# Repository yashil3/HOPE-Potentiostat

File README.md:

# Pocket Potentiostat
IEEE DeCal HOPE Final Project -- Potentiostat for applying cyclic voltammetry to electrolyte

- Blocks A, B, D, and E: uses OPA2277 high-precision operational amplifiers
- Block C: uses TL074 transimpedance amplifier
- Blocks F, G, and H: uses INA128 instrumentational amplifiers
- Block C uses a TL074 Transimpedance Amplifier (TIA). It is cost-effective, but it is not the best option (a really good one would be ~$40)
- May need to fix Rg resistor values based on how much the voltage in the electrodes varies

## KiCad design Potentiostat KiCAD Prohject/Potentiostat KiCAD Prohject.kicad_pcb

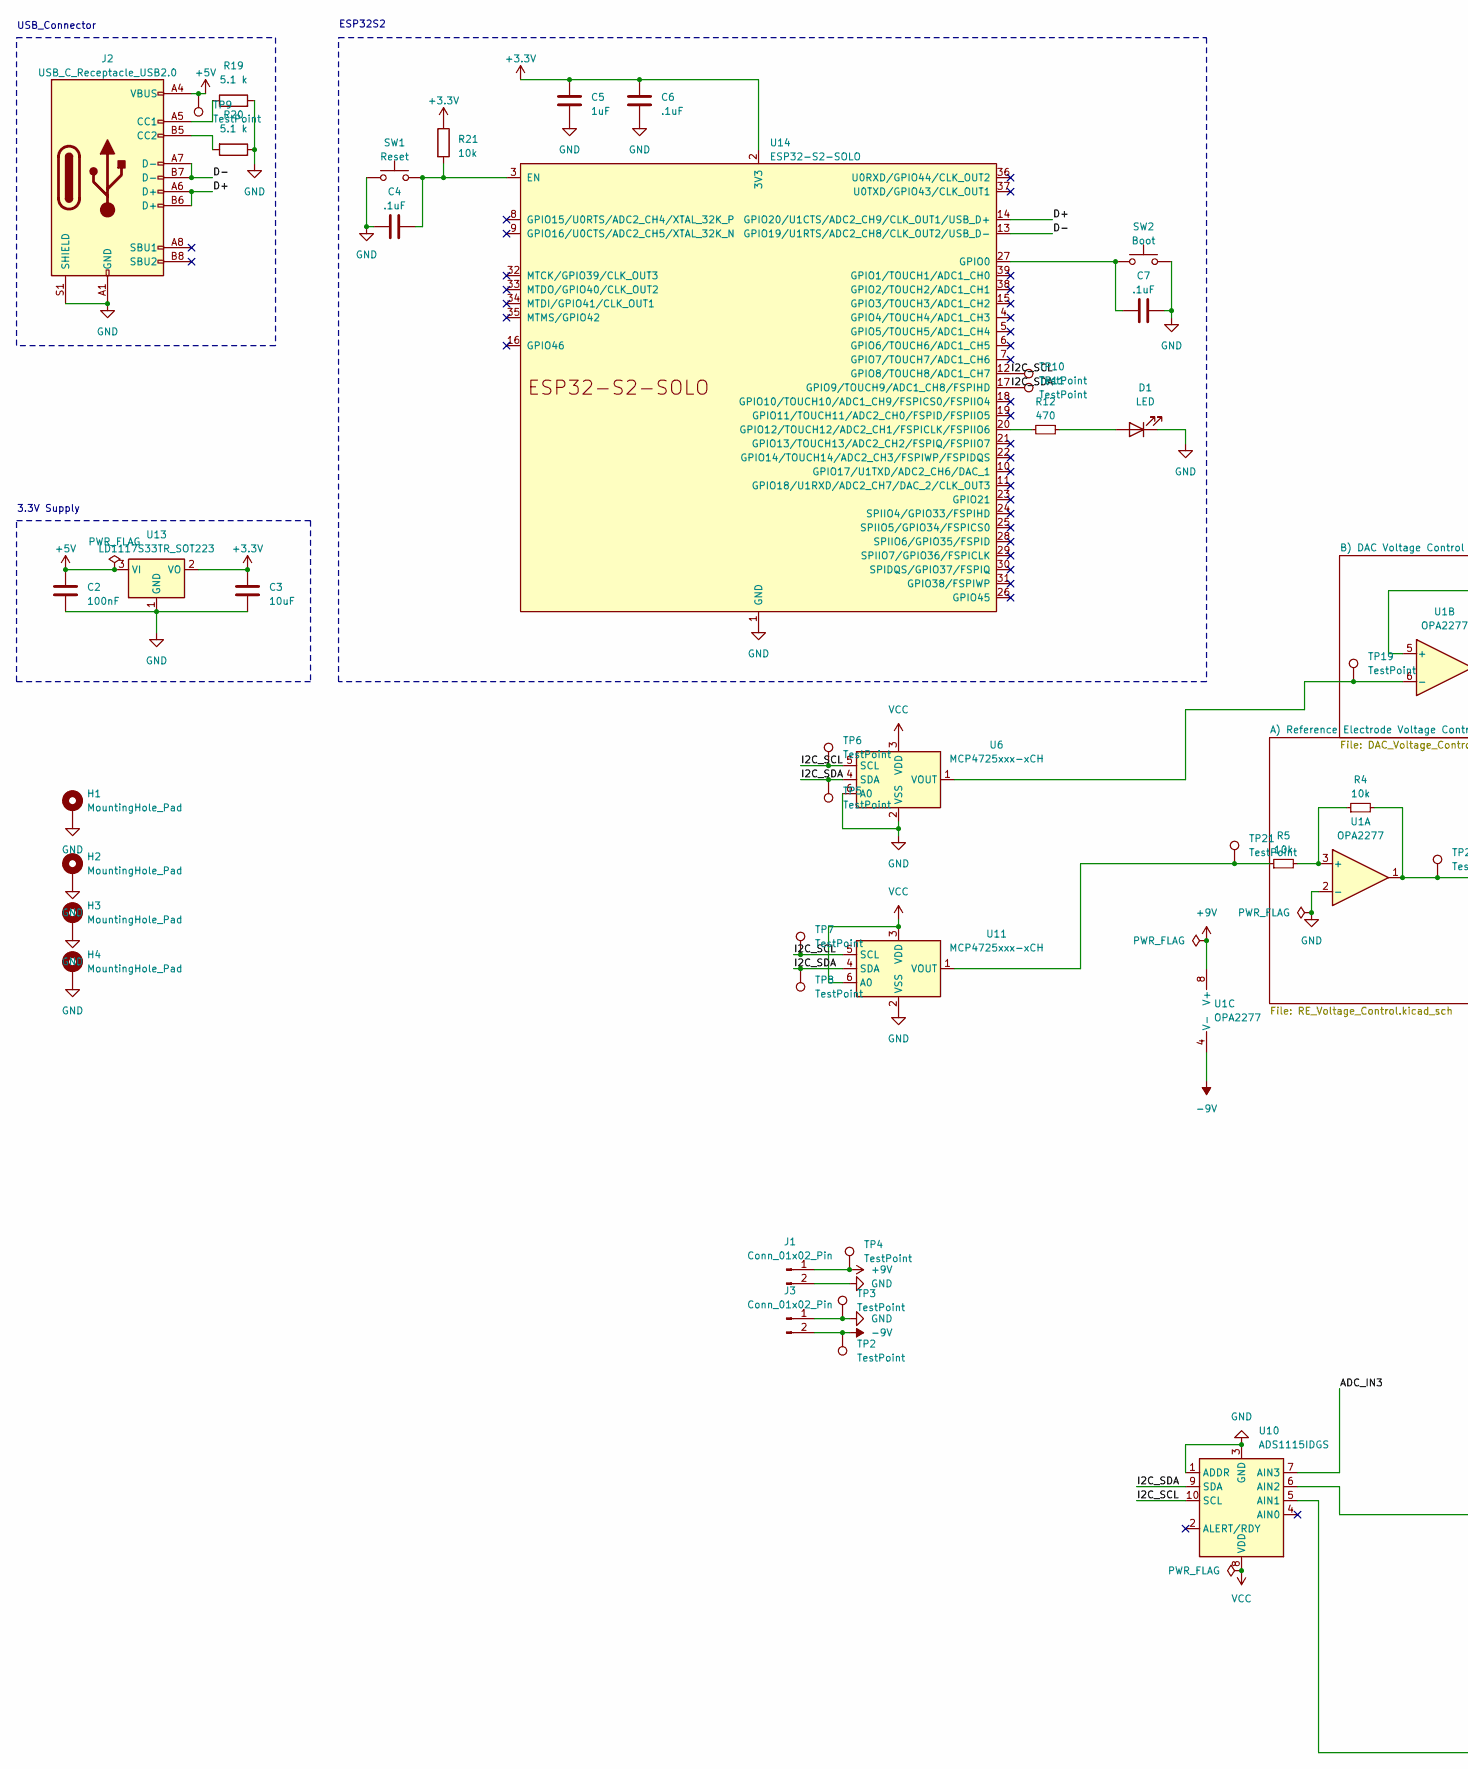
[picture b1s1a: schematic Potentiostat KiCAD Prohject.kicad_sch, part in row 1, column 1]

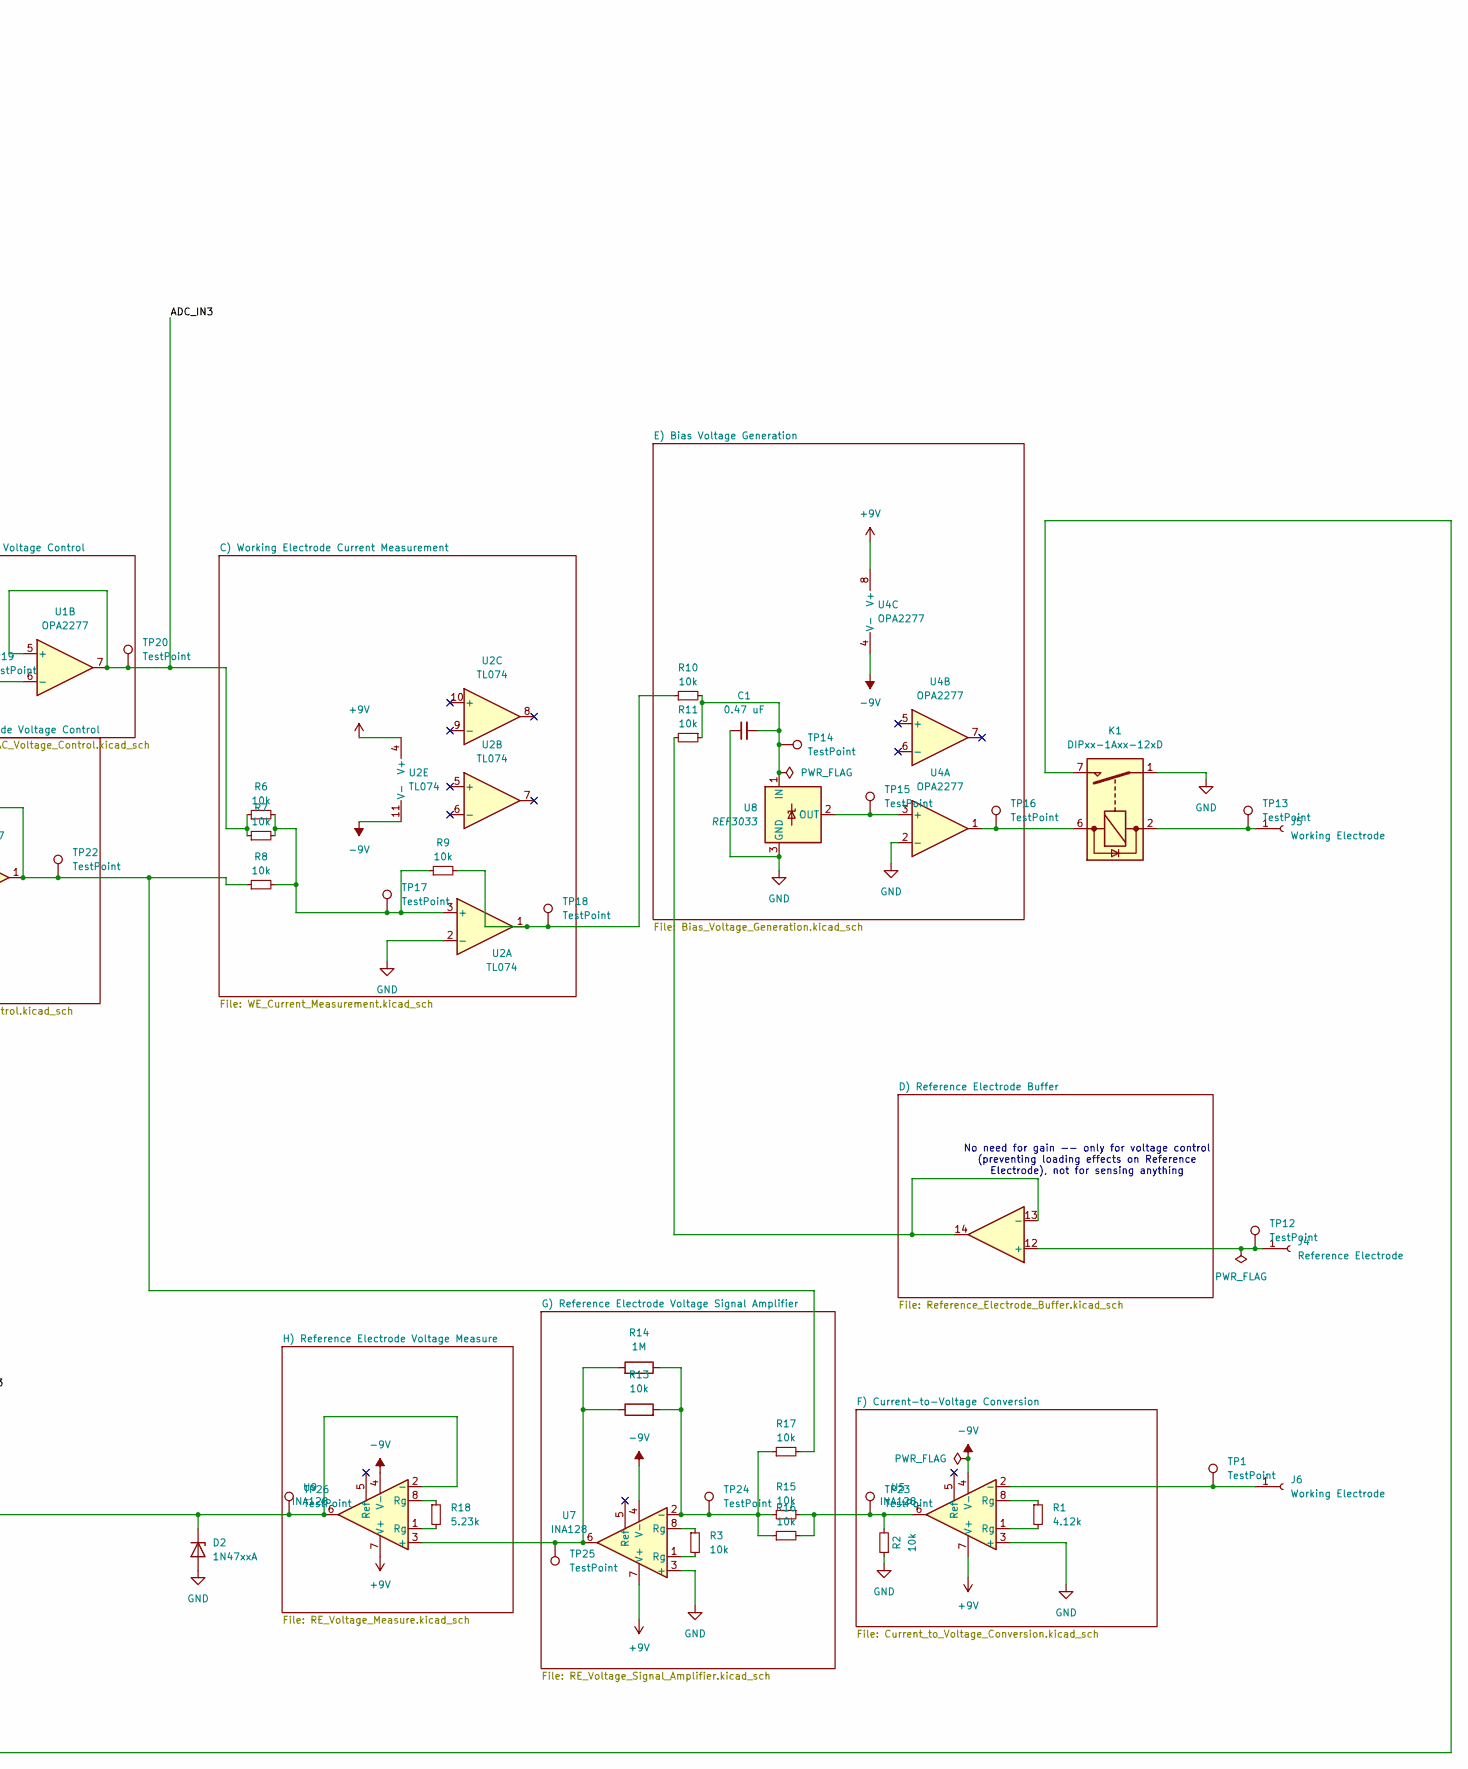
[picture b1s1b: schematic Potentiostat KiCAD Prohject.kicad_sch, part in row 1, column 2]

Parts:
C1: 0.47 uF; CAPC7851084X4N
C2: 100nF; C_0603_1608Metric
C3: 10uF; C_0603_1608Metric
C4, C6, C7: .1uF; C_0603_1608Metric
C5: 1uF; C_0603_1608Metric
D1: LED; LED_0603_1608Metric
D2: 1N47xxA; D_DO-41_SOD81_P10.16mm_Horizontal
H1, H2, H3, H4: MountingHole_Pad
J1, J3: Conn_01x02_Pin; PinHeader_1x02_P2.54mm_Vertical
J2: USB_C_Receptacle_USB2.0; USB_C_Receptacle_GCT_USB4105-xx-A_16P_TopMnt_Horizontal
J4: Reference Electrode; CONN_575-8_KEY
J5, J6: Working Electrode; CONN_575-8_KEY
K1: DIPxx-1Axx-12xD; Relay_StandexMeder_DIP_LowProfile
R1: 4.12k; R_0603_1608Metric
R2, R3, R4, R5, R6, R7, R8, R9, R10, R11, R13, R15, R16, R17, R21: 10k; R_0603_1608Metric
R12: 470; R_0603_1608Metric
R14: 1M; R_0603_1608Metric
R18: 5.23k; R_0603_1608Metric
R19, R20: 5.1 k; R_0603_1608Metric
SW1: Reset; SW_Push_1P1T-SH_NO_CK_KMR2xxG
SW2: Boot; SW_Push_1P1T-SH_NO_CK_KMR2xxG
TP1, TP2, TP3, TP4, TP5, TP6, TP7, TP8, TP9, TP10, TP11, TP12, TP13, TP14, TP15, TP16, TP17, TP18, TP19, TP20, TP21, TP22, TP23, TP24, TP25, TP26: TestPoint; TestPoint_Pad_1.0x1.0mm
U1, U4: OPA2277; SOIC-8_3.9x4.9mm_P1.27mm
U2: TL074; SOIC-14_3.9x8.7mm_P1.27mm
U5, U7, U9: INA128; SOIC-8_3.9x4.9mm_P1.27mm
U6, U11: MCP4725xxx-xCH; SOT-23-6
U8: REF3033; SOT-23
U10: ADS1115IDGS; TSSOP-10_3x3mm_P0.5mm
U13: LD1117S33TR_SOT223; SOT-223-3_TabPin2
U14: ESP32-S2-SOLO

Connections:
+3.3V: C3.1, C5.1, C6.1, R21.1, U13.2 (VO), U14.2 (3V3)
+5V: C2.1, J2.A4 (VBUS), J2.A9 (VBUS), J2.B4 (VBUS), J2.B9 (VBUS), TP9.1, U13.3 (VI)
+9V: J1.1, TP4.1, U1.8 (V+), U2.4 (V+), U4.8 (V+), U5.7 (V+), U7.7 (V+), U9.7 (V+)
-9V: J3.2, TP2.1, U1.4 (V-), U2.11 (V-), U4.4 (V-), U5.4 (V-), U7.4 (V-), U9.4 (V-)
/ADC_IN3: R6.1, R7.1, TP20.1, U1.5 (+), U1.7, U10.7 (AIN3)
/D+: J2.A6 (D+), J2.B6 (D+), U14.14 (GPIO20/U1CTS/ADC2_CH9/CLK_OUT1/USB_D+)
/D-: J2.A7 (D-), J2.B7 (D-), U14.13 (GPIO19/U1RTS/ADC2_CH8/CLK_OUT2/USB_D-)
/I2C_SCL: TP6.1, TP7.1, TP10.1, U6.5 (SCL), U10.10 (SCL), U11.5 (SCL), U14.12 (GPIO8/TOUCH8/ADC1_CH7)
/I2C_SDA: TP5.1, TP8.1, TP11.1, U6.4 (SDA), U10.9 (SDA), U11.4 (SDA), U14.17 (GPIO9/TOUCH9/ADC1_CH8/FSPIHD)
GND: C1.1, C2.2, C3.2, C4.1, C5.2, C6.2, C7.2, D1.1 (K), D2.2 (A), H1.1, H2.1, H3.1, H4.1, J1.2, J2.A1 (GND), J2.A12 (GND), J2.B1 (GND), J2.B12 (GND), J2.S1 (SHIELD), J3.1, K1.1, K1.14, R2.1, R19.2, R20.1, SW1.1, SW2.2, TP3.1, U1.2 (-), U2.2 (-), U4.2 (-), U5.3 (+), U6.2 (VSS), U6.6 (A0), U7.3 (+), U8.3 (GND), U10.1 (ADDR), U10.3 (GND), U11.2 (VSS), U13.1 (GND), U14.1 (GND), U14.40 (GND), U14.41 (GND)
unnamed: D1.2 (A), R12.1
unnamed: D2.1 (K), TP26.1, U9.2 (-), U9.6, U10.6 (AIN2)
unnamed: J2.A5 (CC1), R19.1
unnamed: J2.B5 (CC2), R20.2
unnamed: J4.1, TP12.1, U2.12 (+)
unnamed: J5.1, K1.2, K1.13, TP13.1
unnamed: J6.1, TP1.1, U5.2 (-)
unnamed: K1.6, TP16.1, U4.1
unnamed: R1.1, U5.8 (Rg)
unnamed: R1.2, U5.1 (Rg)
unnamed: R3.1, U7.8 (Rg)
unnamed: R3.2, U7.1 (Rg)
unnamed: R9.2, R10.1, TP18.1, U2.1
unnamed: R2.2, R15.1, R16.2, TP23.1, U5.6
unnamed: R4.2, R8.1, R17.2, TP22.1, U1.1
unnamed: R18.1, U9.8 (Rg)
unnamed: R18.2, U9.1 (Rg)
unnamed: R4.1, R5.2, U1.3 (+)
unnamed: TP19.1, U1.6 (-), U6.1 (VOUT)
unnamed: R6.2, R7.2, R8.2, R9.1, TP17.1, U2.3 (+)
unnamed: R11.2, U2.13 (-), U2.14
unnamed: TP15.1, U4.3 (+), U8.2 (OUT)
unnamed: R13.2, R14.1, R15.2, R16.1, R17.1, TP24.1, U7.2 (-)
unnamed: C1.2, R10.2, R11.1, TP14.1, U8.1 (IN)
unnamed: R13.1, R14.2, TP25.1, U7.6, U9.3 (+)
unnamed: K1.7, K1.8, U10.5 (AIN1)
unnamed: R5.1, TP21.1, U11.1 (VOUT)
unnamed: C4.2, R21.2, SW1.2, U14.3 (EN)
unnamed: C7.1, SW2.1, U14.27 (GPIO0)
unnamed: R12.2, U14.20 (GPIO12/TOUCH12/ADC2_CH1/FSPICLK/FSPIIO6)
VCC: U6.3 (VDD), U10.8 (VDD), U11.3 (VDD), U11.6 (A0)

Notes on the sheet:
USB_Connector
No need for gain -- only for voltage control (preventing loading effects on Reference Electrode), not for sensing anything
3.3V Supply
ESP32S2

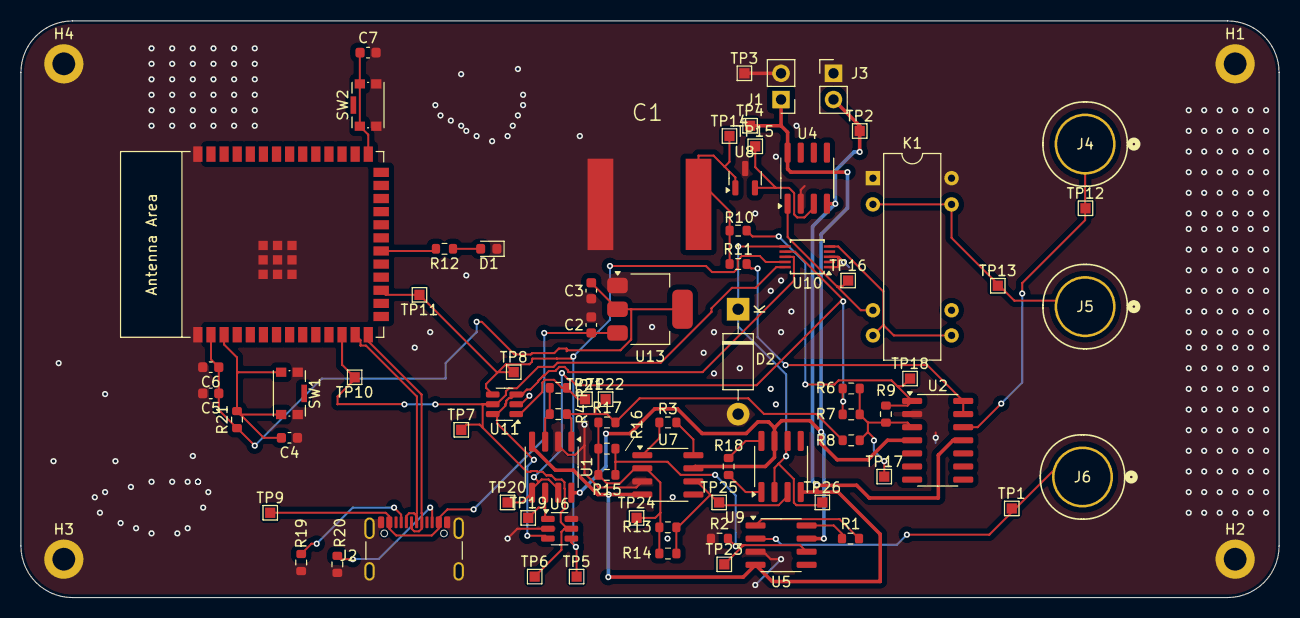
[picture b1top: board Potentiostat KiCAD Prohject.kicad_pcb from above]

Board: 2 copper layers, 121.9 x 55.9 mm, 81 parts (0 on the bottom side), 41 nets.

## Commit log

2025-04-03 initial files
2025-04-03 readme
2025-04-03 changed resistor values
2025-04-03 test push
2025-04-03 Add KiCad files to gitignore
2025-04-03 Add properly configured .gitignore for KiCad files
2025-04-04 completed ESP32 design
2025-04-04 added missing footprints
2025-04-04 add microcontroller stuff
2025-04-09 esp32 solo and cleanup
2025-04-09 updated wires
2025-04-10 Changed resistors and assigned footprints
2025-04-10 Redid layout with ground traces
2025-04-11 we're so back
2025-04-11 almost finished layout -- need test points
2025-04-11 finished!
